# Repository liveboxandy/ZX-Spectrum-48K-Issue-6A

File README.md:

This Kicad 10 project and was only used to create an ibom with tracks to assist in the debugging of faulty boards. While the routing should be correct, the track widths have not been followed exactly, nor have component tolerances. Use at your own risk.

The ZX Spectrum Issue 6A PCB used for this has an MFG date of 8443, a silkscreen FAB revision of SRC168, a topside FAB revision of SRC166 and a solder side FAB revision of SRC167.

The created schematic was based on the physical layout of the PCB and appears to show the DC-DC circuit from a revision 4A PCB where capacitor C79 is before R79 and D19 is after R79 on the -5V line. which is not the same as the schematics available around the web show.

Note that R32 is fitted as a 0R link on this PCB.

Resistor and capacitor values in the schematic are taken from the Service Manual Revision 1.3 that was edited by Brendan Alford and appear to differ in various locations compared to various available schematics. Where they differed I have used the values from the PCB I was given by HappyLittleDiodes(Jim).

For the Ferranti ULA, do not fit R90, C100, C102, C103 and leave LK1, LK2, LK3 and LK4 open.

On the PCB I received, LKU and LKV were also open.

On the board I received,

C30 	22nF		Not Required for Saga ULA

C32 	100nF		Not Required for Saga

C35 	100nF		Not Required for Saga, Saga 10nF

C52/C53 150pF		Not Required for Saga

C67 	100pF		Not Required for Saga

C68-C71 100nF		Not Required for Saga

C76 	22nF		Not Required for Saga

C100	Not Fitted. 	For VHF 10nF

C101 	Not Fitted. 	For VHF 22nF

C102 	Not Fitted

C103 	Not Fitted

R17-R23 470R		Issue 5 Only?

R24 	1K		If TR3 is KSC839 should be 15K

R33 	680R		For Saga 560R

R34 	15R 0.5/1W

R48 	2K2		Not Required for Saga

R49 	10K		Not Required for Saga

R50 	4K7		Not Required for Saga

R51 	2K2		For Saga 1K2

R56 	1K		Not Required for Saga

R63 	1K		Not Required for Saga

R65-R67 10K		Not Required for Saga

R68 	6K8		Not Required for Saga

R69 	10K		Not Required for Saga

R73 	1K		Not Required for Saga

R74/R75 10K		Not Required for Saga

R76/R77 1K		Not Required for Saga

R80-R86 1K		Issue 5 Only?

I would not use these gerbers to manufacture a PCB without a lot more checking as that is NOT why it was done.

Have fun.

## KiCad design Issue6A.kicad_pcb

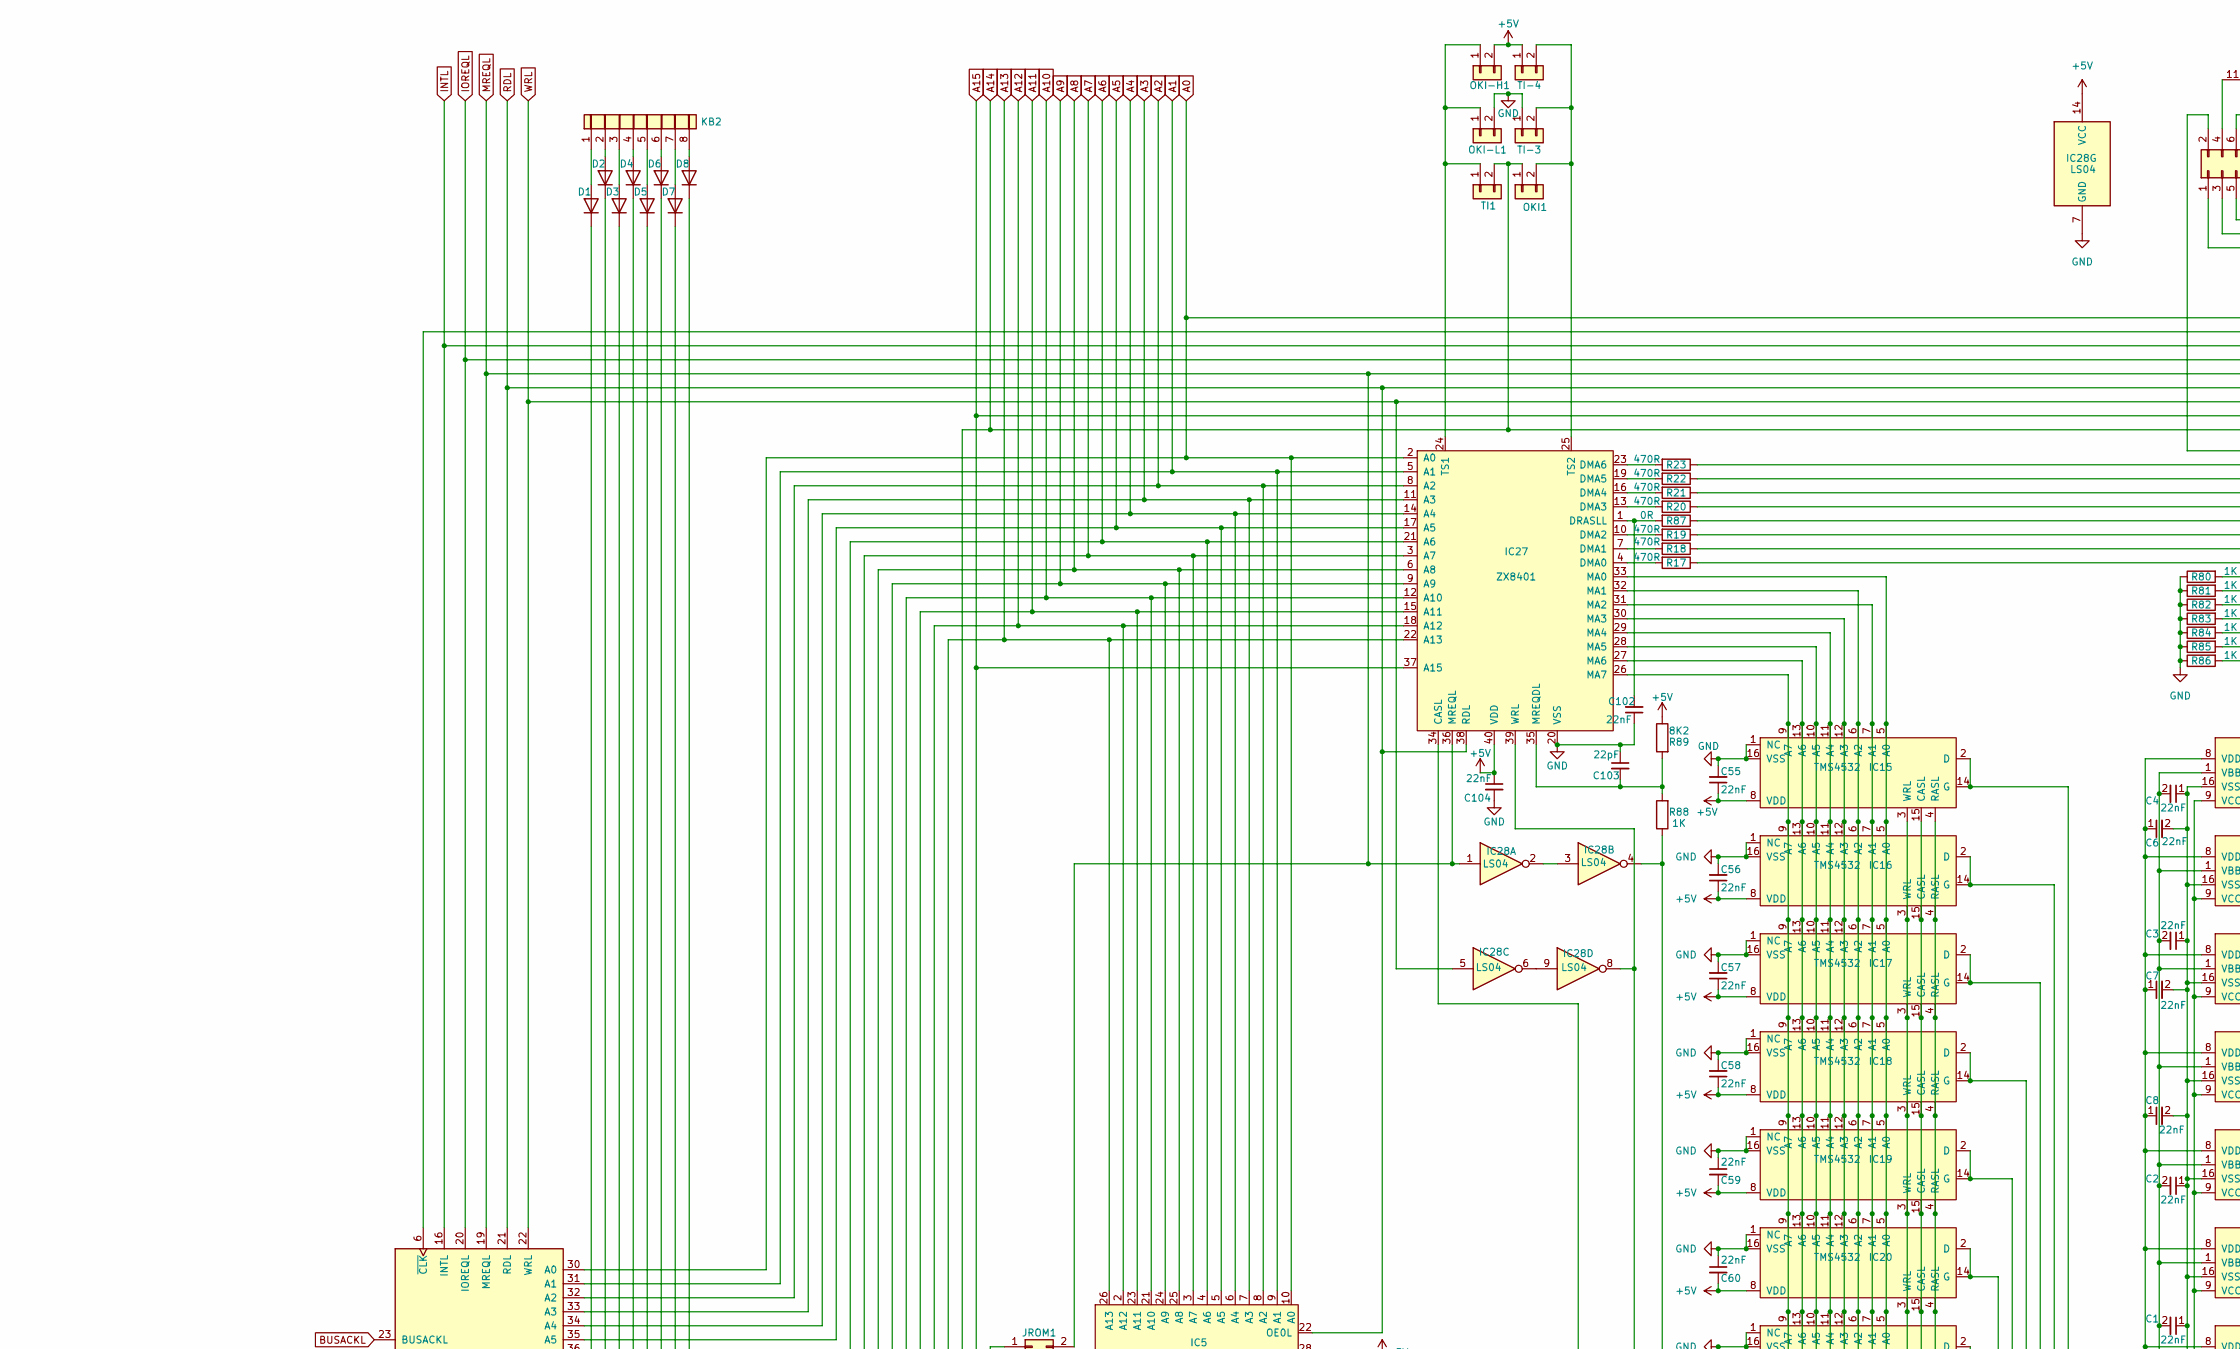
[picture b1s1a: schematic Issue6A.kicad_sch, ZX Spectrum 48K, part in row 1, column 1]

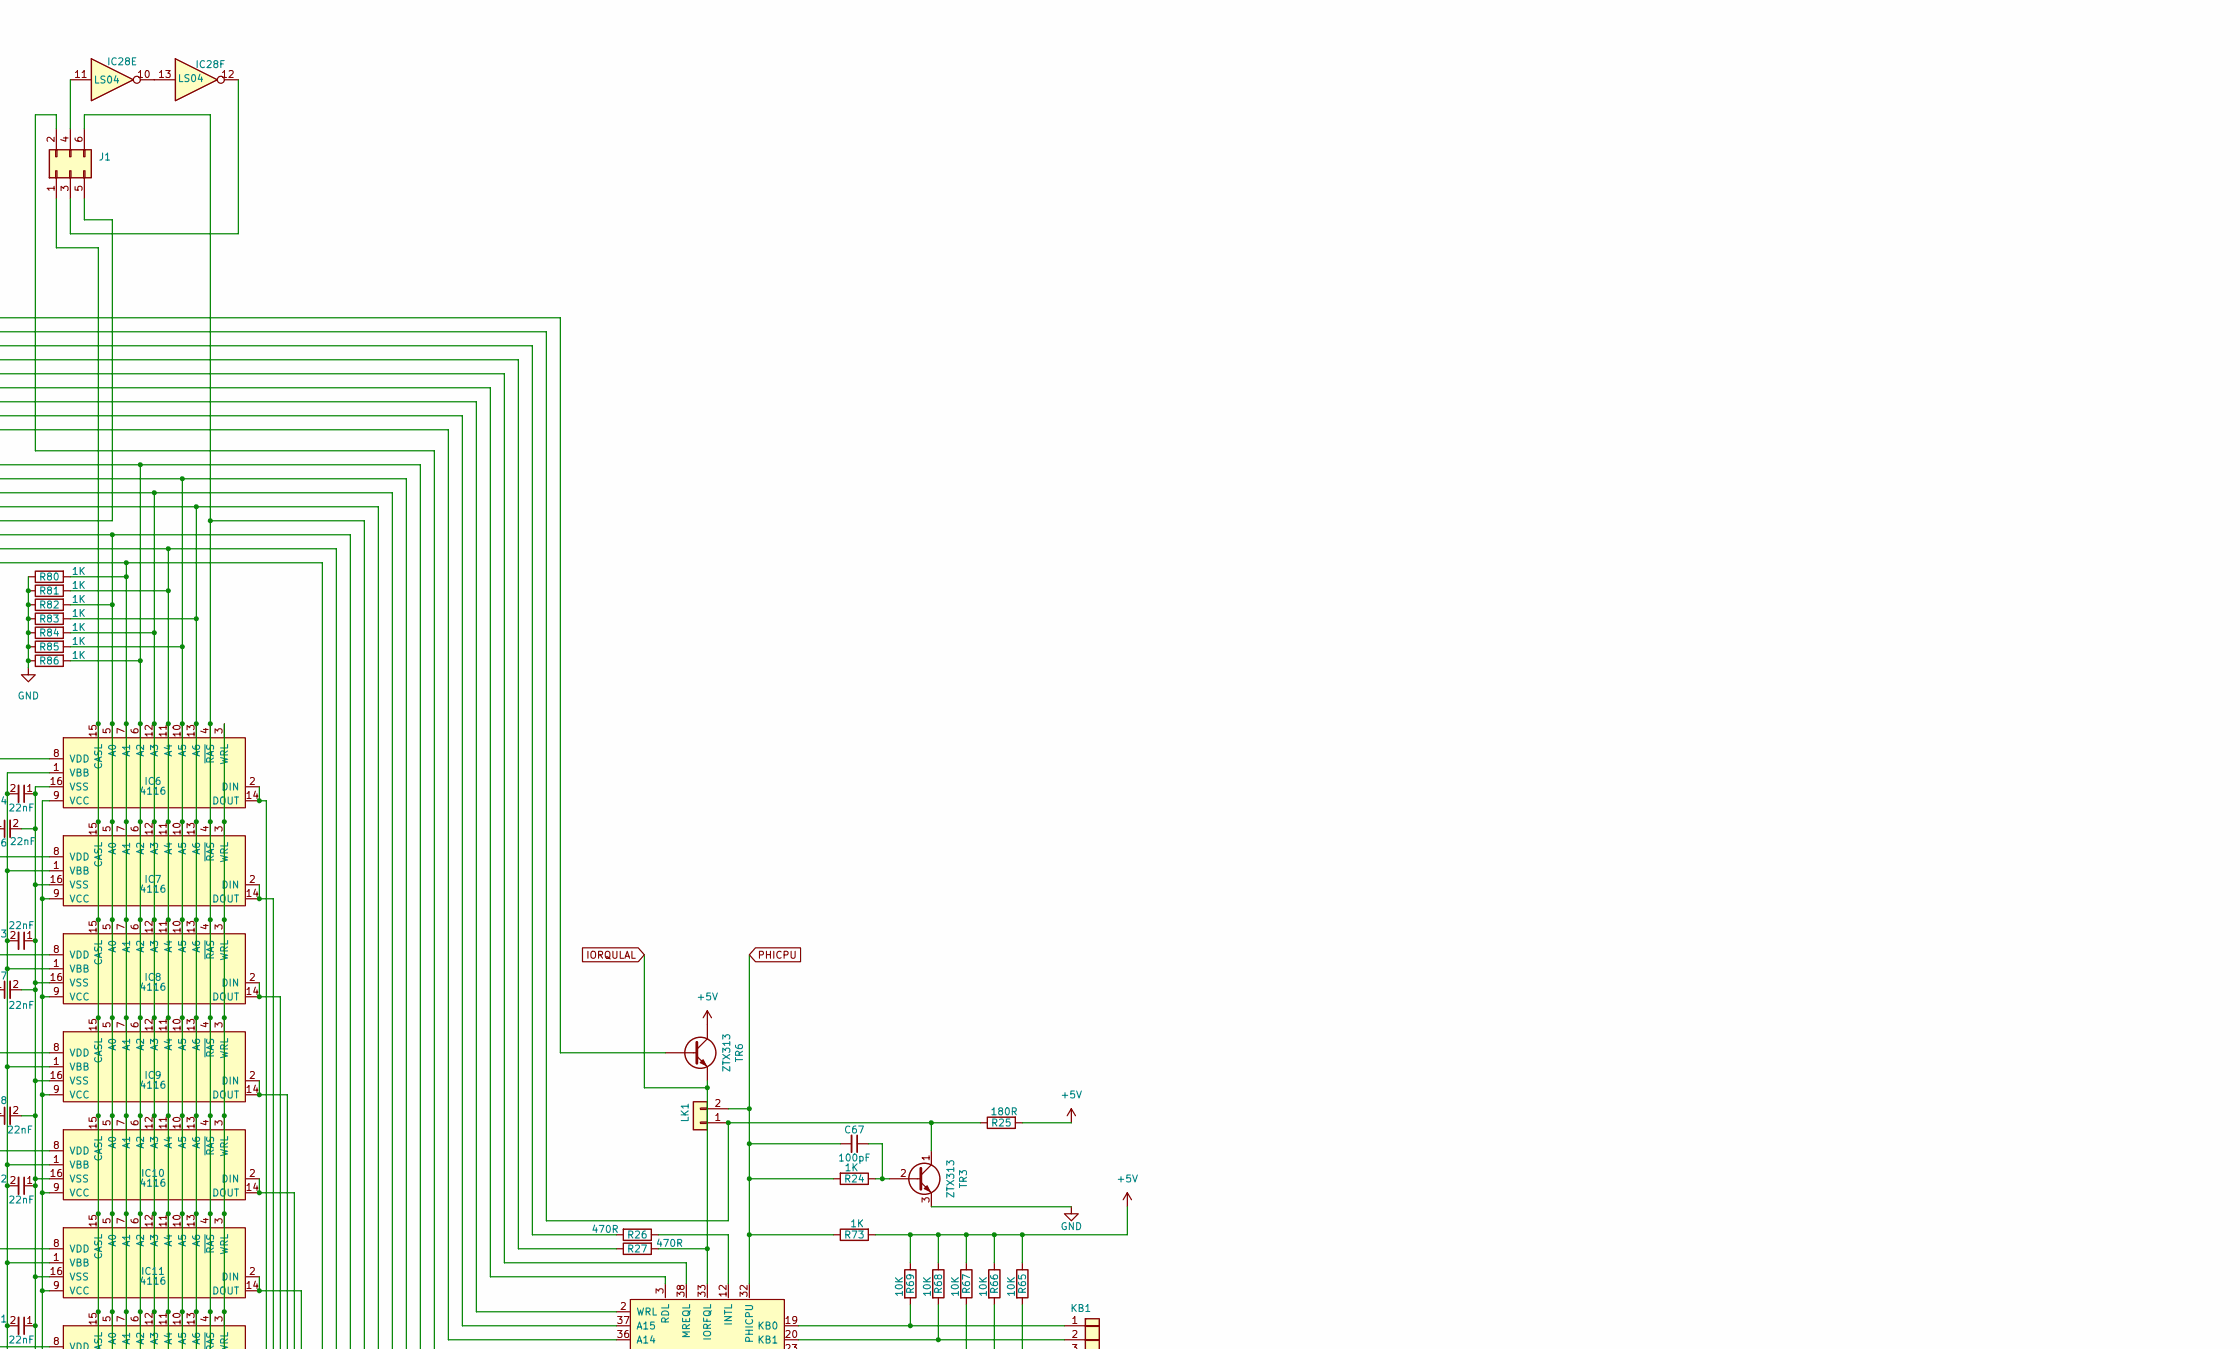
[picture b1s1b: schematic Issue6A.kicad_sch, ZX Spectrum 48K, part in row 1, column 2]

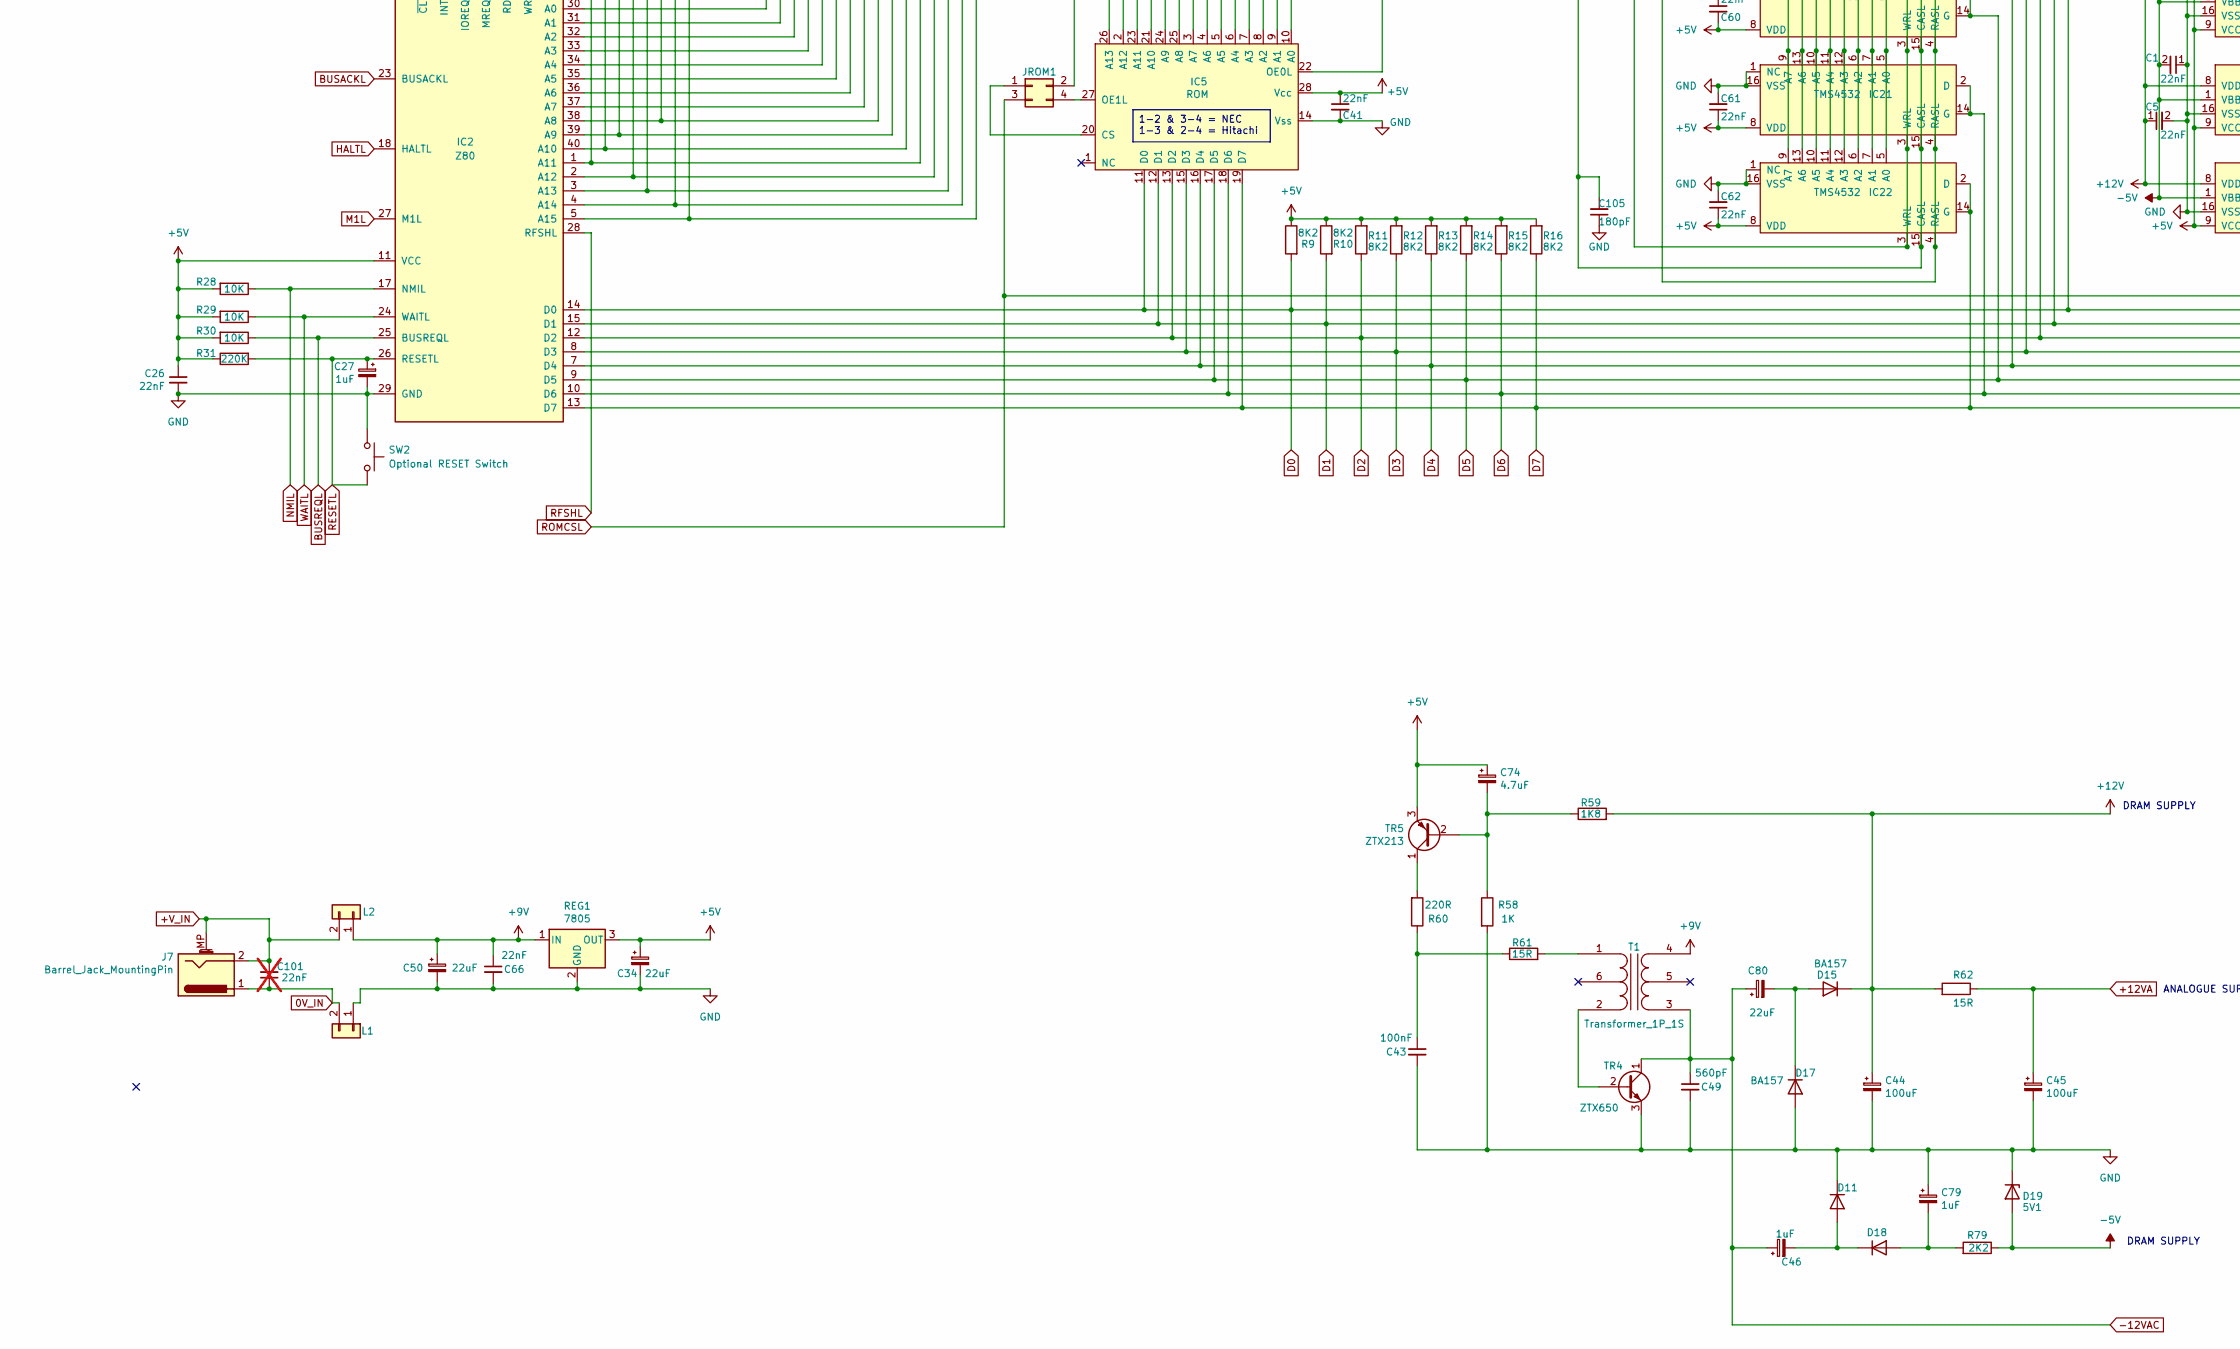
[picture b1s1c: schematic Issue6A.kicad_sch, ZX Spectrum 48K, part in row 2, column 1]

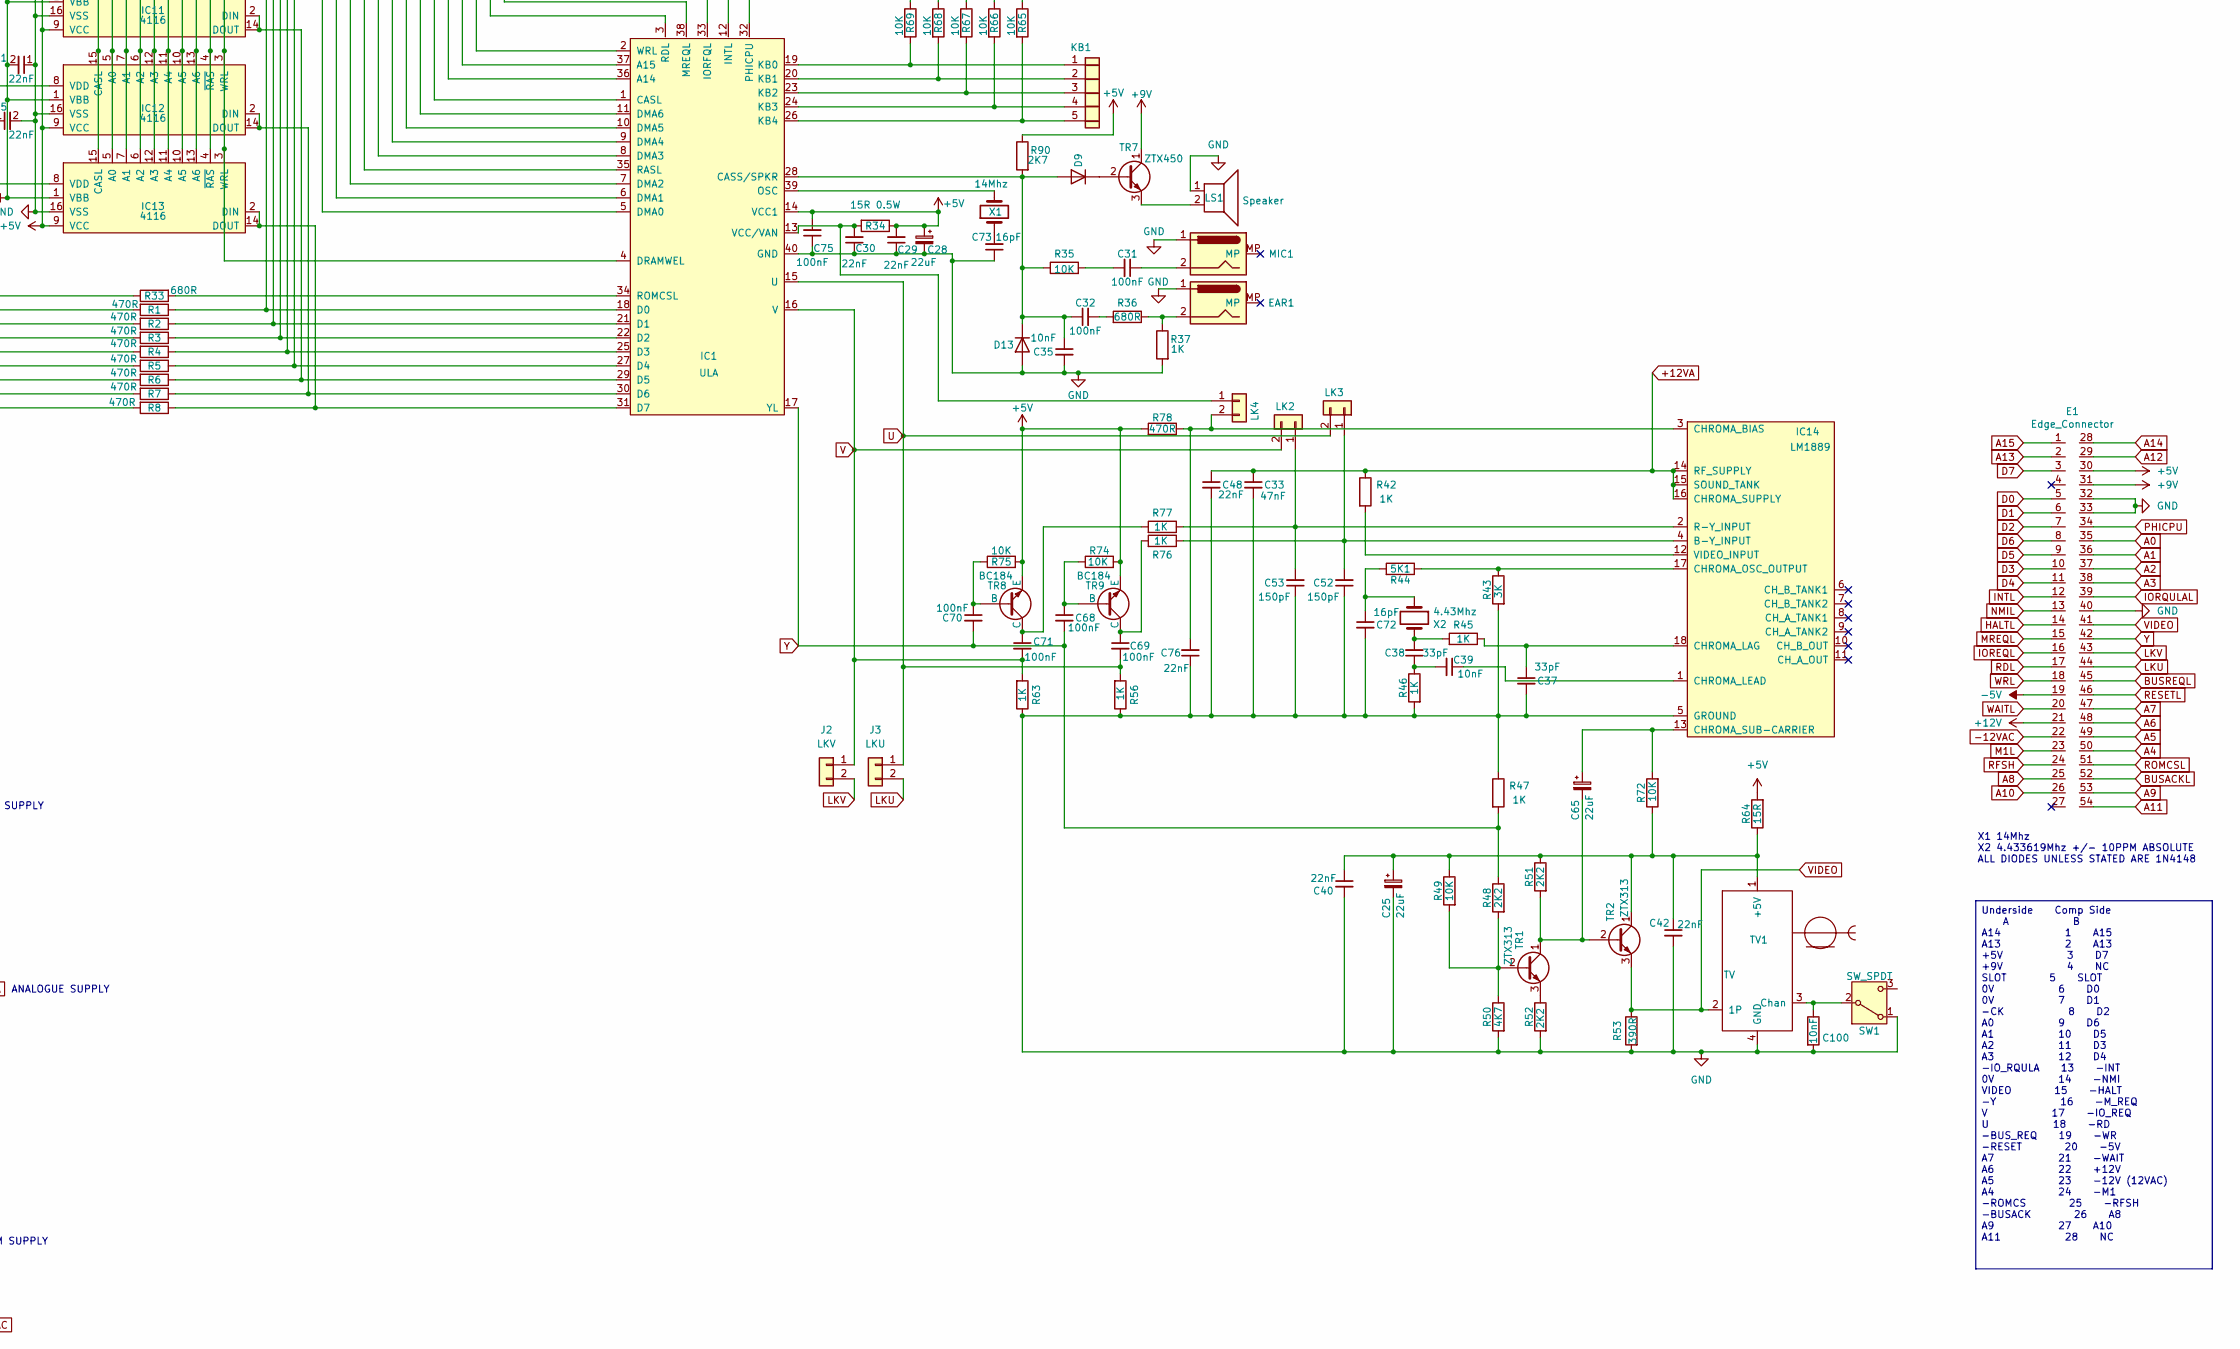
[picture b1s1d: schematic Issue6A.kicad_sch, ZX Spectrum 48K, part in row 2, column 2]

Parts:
C1, C2, C3, C4, C5, C6, C7, C8, C26, C29, C30, C40, C41, C42, C48, C55, C56, C57, C58, C59, C60, C61, C62, C66, C76, C102, C104: 22nF; C_Axial_L3.8mm_D2.6mm_P12.70mm_Horizontal
C25: 22uF; CP_Axial_L11.0mm_D6.0mm_P20.00mm_Horizontal
C27, C46, C79: 1uF; CP_Axial_L11.0mm_D6.0mm_P20.32mm_Horizontal
C28, C34, C50, C65, C80: 22uF; CP_Axial_L11.0mm_D6.0mm_P20.32mm_Horizontal
C31, C32: 100nF; C_Axial_L3.8mm_D2.6mm_P12.40mm_Horizontal
C33: 47nF; C_Axial_L3.8mm_D2.6mm_P12.70mm_Horizontal
C35: 10nF; C_Axial_L3.8mm_D2.6mm_P12.40mm_Horizontal
C37, C38: 33pF; C_Axial_L3.8mm_D2.6mm_P12.70mm_Horizontal
C39: 10nF; C_Axial_L3.8mm_D2.6mm_P12.70mm_Horizontal
C43, C68, C69, C70, C71, C75: 100nF; C_Axial_L3.8mm_D2.6mm_P12.70mm_Horizontal
C44, C45: 100uF; CP_Axial_L11.0mm_D6.0mm_P20.32mm_Horizontal
C49: 560pF; C_Axial_L3.8mm_D2.6mm_P12.70mm_Horizontal
C52, C53: 150pF; C_Axial_L3.8mm_D2.6mm_P12.70mm_Horizontal
C67: 100pF; C_Axial_L3.8mm_D2.6mm_P12.70mm_Horizontal
C72, C73: 16pF; C_Axial_L3.8mm_D2.6mm_P12.70mm_Horizontal
C74: 4.7uF; CP_Axial_L11.0mm_D6.0mm_P20.32mm_Horizontal
C100: 10nF; R_Yageo_L3.6mm_D1.6mm_P12.70mm_Horizontal
C101: 22nF; C_Axial_L3.8mm_D2.6mm_P12.70mm_Horizontal; not fitted
C103: 22pF; C_Axial_L3.8mm_D2.6mm_P12.70mm_Horizontal
C105: 180pF; C_Axial_L3.8mm_D2.6mm_P12.70mm_Horizontal
D1, D2, D3, D4, D5, D6, D7, D8, D9, D11, D18: 1N4148; D_DO-35_SOD27_P12.70mm_Horizontal
D13: 1N4148; D_DO-35_SOD27_P12.40mm_Horizontal
D15, D17: BA157; D_DO-41_SOD81_P12.70mm_Horizontal
D19: 5V1; D_DO-35_SOD27_P12.70mm_Horizontal
E1: Edge_Connector; Edge Connector
EAR1: EAR1; 3.5mm_socket
IC1: ULA; DIP-40_W15.24mm_Socket
IC2: Z80; DIP-40_W15.24mm_Socket
IC5: ROM; DIP-28_W15.24mm_Socket
IC6, IC7, IC8, IC9, IC10, IC11, IC12, IC13: 4116; DIP-16_W7.62mm_Socket
IC14: LM1889; DIP-18_W7.62mm_Socket
IC15, IC16, IC17, IC18, IC19, IC20, IC21, IC22: TMS4532; DIP-16_W7.62mm_Socket
IC27: ZX8401; DIP-40_W15.24mm_Socket
IC28: LS04; DIP-14_W7.62mm_Socket
J1: Conn_02x03_Odd_Even; RASCASLINK
J2: LKV; Link2.54
J3: LKU; Link2.54
J7: Barrel_Jack_MountingPin; BarrelJack_Horizontal
JROM1: JROM; ROM_WireLink
KB1: Keyboard5
KB2: Keyboard8
L1: L1; Wire_Link_7.62mm
L2: L2; Wire_Link_7.62mm
LK1: CLK; KEYSTONE_1430-5
LK2: LK2; Wire_Link_7.62mm
LK3: LK3; Wire_Link_7.62mm
LK4: VCC/VAN; Wire_Link_7.62mm
LS1: Speaker
MIC1: MIC1; 3.5mm_socket
OKI1: OKI; Wire_Link_7.62mm
OKI-H1: OKI-H; Wire_Link_7.62mm
OKI-L1: OKI-L; Wire_Link_7.62mm
R1, R2, R3, R4, R5, R6, R7, R8, R17, R18, R19, R20, R21, R22, R23, R26, R27, R78: 470R; R_Yageo_L3.6mm_D1.6mm_P12.70mm_Horizontal
R9, R10, R11, R12, R13, R14, R15, R16, R89: 8K2; R_Yageo_L3.6mm_D1.6mm_P12.70mm_Horizontal
R24, R42, R45, R46, R47, R56, R58, R63, R73, R76, R77, R80, R81, R82, R83, R84, R85, R86, R88: 1K; R_Yageo_L3.6mm_D1.6mm_P12.70mm_Horizontal
R25: 180R; R_Yageo_L3.6mm_D1.6mm_P12.70mm_Horizontal
R28, R29, R30, R49, R65, R66, R67, R68, R69, R72, R74, R75: 10K; R_Yageo_L3.6mm_D1.6mm_P12.70mm_Horizontal
R31: 220K; R_Yageo_L3.6mm_D1.6mm_P12.70mm_Horizontal
R33: 680R; R_Yageo_L3.6mm_D1.6mm_P12.70mm_Horizontal
R34: 15R 0.5W; R_Axial_DIN0516_L15.5mm_D5.0mm_P20.32mm_Horizontal
R35: 10K; R_Yageo_L3.6mm_D1.6mm_P12.40mm_Horizontal
R36: 680R; R_Yageo_L3.6mm_D1.6mm_P12.40mm_Horizontal
R37: 1K; R_Yageo_L3.6mm_D1.6mm_P12.40mm_Horizontal
R43: 3K; R_Yageo_L3.6mm_D1.6mm_P12.70mm_Horizontal
R44: 5K1; R_Yageo_L3.6mm_D1.6mm_P12.70mm_Horizontal
R48, R51, R52, R79: 2K2; R_Yageo_L3.6mm_D1.6mm_P12.70mm_Horizontal
R50: 4K7; R_Yageo_L3.6mm_D1.6mm_P12.70mm_Horizontal
R53: 390R; R_Yageo_L3.6mm_D1.6mm_P12.70mm_Horizontal
R59: 1K8; R_Yageo_L3.6mm_D1.6mm_P12.70mm_Horizontal
R60: 220R; R_Yageo_L3.6mm_D1.6mm_P12.70mm_Horizontal
R61, R62, R64: 15R; R_Yageo_L3.6mm_D1.6mm_P12.70mm_Horizontal
R87: 0R; R_Yageo_L3.6mm_D1.6mm_P12.70mm_Horizontal
R90: 2K7; R_Yageo_L3.6mm_D1.6mm_P12.70mm_Horizontal
REG1: 7805; TO-220-3_Horizontal_TabDown
SW1: SW_SPDT; SHM1260H
SW2: Optional RESET Switch; PinHeader_1x02_P2.54mm_Vertical
T1: Transformer_1P_1S; Coil
TI1: TI; Wire_Link_7.62mm
TI-3: TI-3; Wire_Link_7.62mm
TI-4: TI-4; Wire_Link_7.62mm
TR1, TR2, TR3, TR6: ZTX313; TO-92Flat
TR4: ZTX650; TO-92Flat
TR5: ZTX213; TO-92Flat
TR7: ZTX450; TO-92Flat
TR8, TR9: BC184; TR9
TV1: TV; Modulator4B
X1: 14Mhz; X1
X2: 4.43Mhz; X2

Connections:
0V_IN: C101.1, J7.1, L1.2
+5V: C26.1, C28.1, C29.2, C34.1, C41.1, C55.1, C56.1, C57.1, C58.1, C59.2, C60.2, C61.1, C62.1, C74.1, C75.2, C104.1, E1.30, IC1.14 (VCC1), IC2.11 (VCC), IC5.28 (Vcc), IC6.9 (VCC), IC7.9 (VCC), IC8.9 (VCC), IC9.9 (VCC), IC10.9 (VCC), IC11.9 (VCC), IC12.9 (VCC), IC13.9 (VCC), IC15.8 (VDD), IC16.8 (VDD), IC17.8 (VDD), IC18.8 (VDD), IC19.8 (VDD), IC20.8 (VDD), IC21.8 (VDD), IC22.8 (VDD), IC27.40 (VDD), IC28.14 (VCC), OKI-H1.2, R9.1, R10.1, R11.2, R12.2, R13.2, R14.2, R15.2, R16.2, R25.2, R28.2, R29.2, R30.2, R31.1, R34.1, R64.2, R65.1, R66.1, R67.1, R68.1, R69.1, R73.2, R74.2, R75.2, R78.2, R89.1, R90.1, REG1.3 (OUT), TI-4.1, TR5.3 (E), TR6.1 (C), TR8.3 (E), TR9.3 (E)
+9V: C50.1, C66.1, E1.31, L2.1, REG1.1 (IN), T1.4 (SB), TR7.1 (C)
+12V: C5.1, C6.1, C7.1, C8.1, C44.1, D15.1 (K), E1.21, IC6.8 (VDD), IC7.8 (VDD), IC8.8 (VDD), IC9.8 (VDD), IC10.8 (VDD), IC11.8 (VDD), IC12.8 (VDD), IC13.8 (VDD), R59.2, R62.2
+12VA: C33.1, C45.1, C48.1, IC14.14 (RF_SUPPLY), IC14.15 (SOUND_TANK), IC14.16 (CHROMA_SUPPLY), R42.1, R62.1
+V_IN: C101.2, J7.2, J7.MP (MountPin_MP), L2.2
-5V: C1.2, C2.2, C3.2, C4.2, D19.2 (A), E1.19, IC6.1 (VBB), IC7.1 (VBB), IC8.1 (VBB), IC9.1 (VBB), IC10.1 (VBB), IC11.1 (VBB), IC12.1 (VBB), IC13.1 (VBB), R79.1
-12VAC: C46.1, C49.1, C80.1, E1.22, T1.3 (SA), TR4.1 (C)
A0: E1.35, IC2.30 (A0), IC5.10 (A0), IC27.2 (A0), TR6.2 (B)
A1: E1.36, IC2.31 (A1), IC5.9 (A1), IC27.5 (A1)
A2: E1.37, IC2.32 (A2), IC5.8 (A2), IC27.8 (A2)
A3: E1.38, IC2.33 (A3), IC5.7 (A3), IC27.11 (A3)
A4: E1.50, IC2.34 (A4), IC5.6 (A4), IC27.14 (A4)
A5: E1.49, IC2.35 (A5), IC5.5 (A5), IC27.17 (A5)
A6: E1.48, IC2.36 (A6), IC5.4 (A6), IC27.21 (A6)
A7: E1.47, IC2.37 (A7), IC5.3 (A7), IC27.3 (A7)
A8: D6.1 (K), E1.25, IC2.38 (A8), IC5.25 (A8), IC27.6 (A8)
A9: D3.1 (K), E1.53, IC2.39 (A9), IC5.24 (A9), IC27.9 (A9)
A10: D2.1 (K), E1.26, IC2.40 (A10), IC5.21 (A10), IC27.12 (A10)
A11: D1.1 (K), E1.54, IC2.1 (A11), IC5.23 (A11), IC27.15 (A11)
A12: D4.1 (K), E1.29, IC2.2 (A12), IC5.2 (A12), IC27.18 (A12)
A13: D5.1 (K), E1.2, IC2.3 (A13), IC5.26 (A13), IC27.22 (A13)
A14: D7.1 (K), E1.28, IC1.36 (A14), IC2.4 (A14), OKI1.1, TI1.2
A15: D8.1 (K), E1.1, IC1.37 (A15), IC2.5 (A15), IC27.37 (A15)
BUSACKL: E1.52, IC2.23 (BUSACKL)
BUSREQL: E1.45, IC2.25 (BUSREQL), R30.1
D0: E1.5, IC2.14 (D0), IC5.11 (D0), IC15.2 (D), IC15.14 (G), R1.2, R9.2
D1: E1.6, IC2.15 (D1), IC5.12 (D1), IC16.2 (D), IC16.14 (G), R2.2, R10.2
D2: E1.7, IC2.12 (D2), IC5.13 (D2), IC17.2 (D), IC17.14 (G), R3.2, R11.1
D3: E1.10, IC2.8 (D3), IC5.15 (D3), IC18.2 (D), IC18.14 (G), R4.2, R12.1
D4: E1.11, IC2.7 (D4), IC5.16 (D4), IC19.2 (D), IC19.14 (G), R5.2, R13.1
D5: E1.9, IC2.9 (D5), IC5.17 (D5), IC20.2 (D), IC20.14 (G), R6.2, R14.1
D6: E1.8, IC2.10 (D6), IC5.18 (D6), IC21.2 (D), IC21.14 (G), R7.2, R15.1
D7: E1.3, IC2.13 (D7), IC5.19 (D7), IC22.2 (D), IC22.14 (G), R8.2, R16.1
GND: C1.1, C2.1, C3.1, C4.1, C5.2, C6.2, C7.2, C8.2, C25.2, C26.2, C27.2, C28.2, C29.1, C30.1, C33.2, C34.2, C35.2, C37.2, C40.2, C41.2, C42.2, C43.2, C44.2, C45.2, C48.2, C49.2, C50.2, C52.1, C53.1, C55.2, C56.2, C57.2, C58.2, C59.1, C60.1, C61.2, C62.2, C66.2, C72.2, C73.1, C75.1, C76.1, C79.1, C100.2, C102.1, C103.1, C104.2, C105.1, D11.1 (K), D13.2 (A), D17.2 (A), D19.1 (K), E1.32, E1.33, E1.40, EAR1.1, IC1.40 (GND), IC2.29 (GND), IC5.14 (Vss), IC6.16 (VSS), IC7.16 (VSS), IC8.16 (VSS), IC9.16 (VSS), IC10.16 (VSS), IC11.16 (VSS), IC12.16 (VSS), IC13.16 (VSS), IC14.5 (GROUND), IC15.1 (NC), IC15.16 (VSS), IC16.1 (NC), IC16.16 (VSS), IC17.1 (NC), IC17.16 (VSS), IC18.1 (NC), IC18.16 (VSS), IC19.1 (NC), IC19.16 (VSS), IC20.1 (NC), IC20.16 (VSS), IC21.1 (NC), IC21.16 (VSS), IC22.1 (NC), IC22.16 (VSS), IC27.20 (VSS), IC28.7 (GND), L1.1, LS1.1, MIC1.1, OKI-L1.2, R37.2, R43.2, R46.2, R47.1, R50.2, R52.2, R53.2, R56.1, R58.2, R63.1, R80.1, R81.1, R82.1, R83.1, R84.1, R85.1, R86.1, REG1.2 (GND), SW1.1 (A), SW2.1, TI-3.1, TR3.3 (E), TR4.3 (E), TV1.4 (GND)
HALTL: E1.14, IC2.18 (HALTL)
INTL: E1.12, IC2.16 (INTL), R26.2
IOREQL: E1.16, IC2.20 (IOREQL), R27.1
IORQULAL: E1.39, IC1.33 (IORFQL), R27.2, TR6.3 (E)
LKU: E1.44, J3.2
LKV: E1.43, J2.2
M1L: E1.23, IC2.27 (M1L)
MREQL: E1.15, IC1.38 (MREQL), IC2.19 (MREQL), IC27.36 (MREQL), IC28.1, JROM1.2
NMIL: E1.13, IC2.17 (NMIL), R28.1
unnamed: C31.1, MIC1.2
unnamed: C31.2, R35.2
unnamed: C32.2, R36.2
unnamed: C38.1, C39.2, R46.1
unnamed: C38.2, R45.2, X2.2
unnamed: C43.1, R60.1, R61.1
unnamed: C72.1, R44.2, X2.1
unnamed: C73.2, X1.1
unnamed: D1.2 (A), KB2.1
unnamed: D2.2 (A), KB2.2
unnamed: D3.2 (A), KB2.3
unnamed: D4.2 (A), KB2.4
unnamed: D5.2 (A), KB2.5
unnamed: D6.2 (A), KB2.6
unnamed: D7.2 (A), KB2.7
unnamed: D8.2 (A), KB2.8
unnamed: D9.1 (K), TR7.2 (B)
unnamed: C46.2, D11.2 (A), D18.1 (K)
unnamed: C32.1, C35.1, D9.2 (A), D13.1 (K), IC1.28 (CASS/SPKR), R35.1, R90.2
unnamed: C80.2, D15.2 (A), D17.1 (K)
unnamed: C79.2, D18.2 (A), R79.2
unnamed: EAR1.2, R36.1, R37.1
unnamed: IC1.1 (CASL), J1.2
unnamed: IC1.18 (D0), IC6.2 (DIN), IC6.14 (DOUT), R1.1
unnamed: IC1.21 (D1), IC7.2 (DIN), IC7.14 (DOUT), R2.1
unnamed: IC1.22 (D2), IC8.2 (DIN), IC8.14 (DOUT), R3.1
unnamed: IC1.25 (D3), IC9.2 (DIN), IC9.14 (DOUT), R4.1
unnamed: IC1.27 (D4), IC10.2 (DIN), IC10.14 (DOUT), R5.1
unnamed: IC1.29 (D5), IC11.2 (DIN), IC11.14 (DOUT), R6.1
unnamed: IC1.30 (D6), IC12.2 (DIN), IC12.14 (DOUT), R7.1
unnamed: IC1.31 (D7), IC13.2 (DIN), IC13.14 (DOUT), R8.1
unnamed: IC1.5 (DMA0), IC6.7 (A1), IC7.7 (A1), IC8.7 (A1), IC9.7 (A1), IC10.7 (A1), IC11.7 (A1), IC12.7 (A1), IC13.7 (A1), R17.1, R80.2
unnamed: IC1.6 (DMA1), IC6.11 (A4), IC7.11 (A4), IC8.11 (A4), IC9.11 (A4), IC10.11 (A4), IC11.11 (A4), IC12.11 (A4), IC13.11 (A4), R18.1, R81.2
unnamed: IC1.7 (DMA2), IC6.5 (A0), IC7.5 (A0), IC8.5 (A0), IC9.5 (A0), IC10.5 (A0), IC11.5 (A0), IC12.5 (A0), IC13.5 (A0), R19.1, R82.2
unnamed: IC1.8 (DMA3), IC6.13 (A6), IC7.13 (A6), IC8.13 (A6), IC9.13 (A6), IC10.13 (A6), IC11.13 (A6), IC12.13 (A6), IC13.13 (A6), R20.1, R83.2
unnamed: IC1.9 (DMA4), IC6.12 (A3), IC7.12 (A3), IC8.12 (A3), IC9.12 (A3), IC10.12 (A3), IC11.12 (A3), IC12.12 (A3), IC13.12 (A3), R21.1, R84.2
unnamed: IC1.10 (DMA5), IC6.10 (A5), IC7.10 (A5), IC8.10 (A5), IC9.10 (A5), IC10.10 (A5), IC11.10 (A5), IC12.10 (A5), IC13.10 (A5), R22.1, R85.2
unnamed: IC1.11 (DMA6), IC6.6 (A2), IC7.6 (A2), IC8.6 (A2), IC9.6 (A2), IC10.6 (A2), IC11.6 (A2), IC12.6 (A2), IC13.6 (A2), R23.1, R86.2
unnamed: IC1.4 (DRAMWEL), IC6.3 (WRL), IC7.3 (WRL), IC8.3 (WRL), IC9.3 (WRL), IC10.3 (WRL), IC11.3 (WRL), IC12.3 (WRL), IC13.3 (WRL)
unnamed: IC1.12 (INTL), R26.1
unnamed: IC1.19 (KB0), KB1.1, R69.2
unnamed: IC1.20 (KB1), KB1.2, R68.2
unnamed: IC1.23 (KB2), KB1.3, R67.2
unnamed: IC1.24 (KB3), KB1.4, R66.2
unnamed: IC1.26 (KB4), KB1.5, R65.2
unnamed: IC1.39 (OSC), X1.2
unnamed: IC1.35 (RASL), IC6.4 (~RAS), IC7.4 (~RAS), IC8.4 (~RAS), IC9.4 (~RAS), IC10.4 (~RAS), IC11.4 (~RAS), IC12.4 (~RAS), IC13.4 (~RAS), J1.6
unnamed: IC1.34 (ROMCSL), R33.2
unnamed: C30.2, IC1.13 (VCC/VAN), LK4.1, R34.2
unnamed: IC2.6 (~CLK), LK1.1, R25.1, TR3.1 (C)
unnamed: IC5.20 (CS), JROM1.1
unnamed: IC5.27 (OE1L), JROM1.4
unnamed: IC6.15 (CASL), IC7.15 (CASL), IC8.15 (CASL), IC9.15 (CASL), IC10.15 (CASL), IC11.15 (CASL), IC12.15 (CASL), IC13.15 (CASL), J1.1
unnamed: C52.2, IC14.4 (B-Y_INPUT), LK3.1, R76.1
unnamed: C76.2, IC14.3 (CHROMA_BIAS), LK4.2, R78.1
unnamed: C37.1, IC14.18 (CHROMA_LAG), R45.1
unnamed: C39.1, IC14.1 (CHROMA_LEAD)
unnamed: IC14.17 (CHROMA_OSC_OUTPUT), R43.1, R44.1
unnamed: C65.1, IC14.13 (CHROMA_SUB-CARRIER), R72.2
unnamed: C53.2, IC14.2 (R-Y_INPUT), LK2.1, R77.1
unnamed: IC14.12 (VIDEO_INPUT), R42.2
unnamed: IC15.5 (A0), IC16.5 (A0), IC17.5 (A0), IC18.5 (A0), IC19.5 (A0), IC20.5 (A0), IC21.5 (A0), IC22.5 (A0), IC27.33 (MA0)
unnamed: IC15.7 (A1), IC16.7 (A1), IC17.7 (A1), IC18.7 (A1), IC19.7 (A1), IC20.7 (A1), IC21.7 (A1), IC22.7 (A1), IC27.31 (MA2)
unnamed: IC15.6 (A2), IC16.6 (A2), IC17.6 (A2), IC18.6 (A2), IC19.6 (A2), IC20.6 (A2), IC21.6 (A2), IC22.6 (A2), IC27.32 (MA1)
unnamed: IC15.12 (A3), IC16.12 (A3), IC17.12 (A3), IC18.12 (A3), IC19.12 (A3), IC20.12 (A3), IC21.12 (A3), IC22.12 (A3), IC27.30 (MA3)
unnamed: IC15.11 (A4), IC16.11 (A4), IC17.11 (A4), IC18.11 (A4), IC19.11 (A4), IC20.11 (A4), IC21.11 (A4), IC22.11 (A4), IC27.29 (MA4)
unnamed: IC15.10 (A5), IC16.10 (A5), IC17.10 (A5), IC18.10 (A5), IC19.10 (A5), IC20.10 (A5), IC21.10 (A5), IC22.10 (A5), IC27.28 (MA5)
unnamed: IC15.13 (A6), IC16.13 (A6), IC17.13 (A6), IC18.13 (A6), IC19.13 (A6), IC20.13 (A6), IC21.13 (A6), IC22.13 (A6), IC27.27 (MA6)
unnamed: IC15.9 (A7), IC16.9 (A7), IC17.9 (A7), IC18.9 (A7), IC19.9 (A7), IC20.9 (A7), IC21.9 (A7), IC22.9 (A7), IC27.26 (MA7)
unnamed: C105.2, IC15.15 (CASL), IC16.15 (CASL), IC17.15 (CASL), IC18.15 (CASL), IC19.15 (CASL), IC20.15 (CASL), IC21.15 (CASL), IC22.15 (CASL), IC27.34 (CASL)
unnamed: IC15.4 (RASL), IC16.4 (RASL), IC17.4 (RASL), IC18.4 (RASL), IC19.4 (RASL), IC20.4 (RASL), IC21.4 (RASL), IC22.4 (RASL), IC28.4, R88.1
unnamed: IC15.3 (WRL), IC16.3 (WRL), IC17.3 (WRL), IC18.3 (WRL), IC19.3 (WRL), IC20.3 (WRL), IC21.3 (WRL), IC22.3 (WRL), IC27.39 (WRL), IC28.8
unnamed: IC27.4 (DMA0), R17.2
unnamed: IC27.7 (DMA1), R18.2
unnamed: IC27.10 (DMA2), R19.2
unnamed: IC27.13 (DMA3), R20.2
unnamed: IC27.16 (DMA4), R21.2
unnamed: IC27.19 (DMA5), R22.2
unnamed: IC27.23 (DMA6), R23.2
unnamed: C102.2, IC27.1 (DRASLL), R87.2
unnamed: C103.2, IC27.35 (MREQDL), R88.2, R89.2
unnamed: IC27.24 (TS1), OKI-H1.1, OKI-L1.1, TI1.1
unnamed: IC27.25 (TS2), OKI1.2, TI-3.2, TI-4.2
unnamed: IC28.2, IC28.3
unnamed: IC28.6, IC28.9
unnamed: IC28.10, IC28.13
unnamed: IC28.12, J1.3
unnamed: IC28.11, J1.4
unnamed: J1.5, R87.1
unnamed: C100.1, SW1.2 (B), TV1.3 (Chan)
unnamed: R61.2, T1.1 (AA)
unnamed: T1.2 (AB), TR4.2 (B)
unnamed: R48.2, R49.2, R50.1, TR1.2 (B)
unnamed: C65.2, R51.2, TR1.1 (C), TR2.2 (B)
unnamed: R52.1, TR1.3 (E)
unnamed: C25.1, C40.1, C42.1, R49.1, R51.1, R64.1, R72.1, TR2.1 (C), TV1.1 (+5V)
unnamed: C67.1, R24.1, TR3.2 (B)
unnamed: C74.2, R58.1, R59.1, TR5.2 (B)
unnamed: R60.2, TR5.1 (C)
unnamed: LS1.2, TR7.3 (E)
unnamed: C70.1, R75.1, TR8.2 (B)
unnamed: C71.1, R77.2, TR8.1 (C)
unnamed: C68.1, R74.1, TR9.2 (B)
unnamed: C69.1, R76.2, TR9.1 (C)
PHICPU: C67.2, E1.34, IC1.32 (PHICPU), LK1.2, R24.2, R73.1
RDL: E1.17, IC1.3 (RDL), IC2.21 (RDL), IC5.22 (OE0L), IC27.38 (RDL)
RESETL: C27.1, E1.46, IC2.26 (RESETL), R31.2, SW2.2
RFSH: E1.24
RFSHL: IC2.28 (RFSHL)
ROMCSL: E1.51, JROM1.3, R33.1
U: C69.2, IC1.15 (U), J3.1, LK3.2, R56.2
V: C71.2, IC1.16 (V), J2.1, LK2.2, R63.2
VIDEO: E1.41, R53.1, TR2.3 (E), TV1.2 (1P)
WAITL: E1.20, IC2.24 (WAITL), R29.1
WRL: E1.18, IC1.2 (WRL), IC2.22 (WRL), IC28.5
Y: C68.2, C70.2, E1.42, IC1.17 (YL), R47.2, R48.1

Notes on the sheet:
X1 14Mhz X2 4.433619Mhz +/- 10PPM ABSOLUTE ALL DIODES UNLESS STATED ARE 1N4148
DRAM SUPPLY
ANALOGUE SUPPLY
Underside Comp Side A B A14 1 A15 A13 2 A13 +5V 3 D7 +9V 4 NC SLOT 5 SLOT 0V 6 D0 0V 7 D1 -CK 8 D2 A0 9 D6 A1 10 D5 A2 11 D3 A3 12 D4 -IO_RQULA 13 -INT 0V 14 -NMI VIDEO 15 -HALT -Y 16 -M_REQ V 17 -IO_REQ U 18 -RD -BUS_REQ 19 -WR -RESET 20 -5V A7 21 -WAIT A6 22 +12V A5 23 -12V (12VAC) A4 24 -M1 -ROM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
1-2 & 3-4 = NEC 1-3 & 2-4 = Hitachi

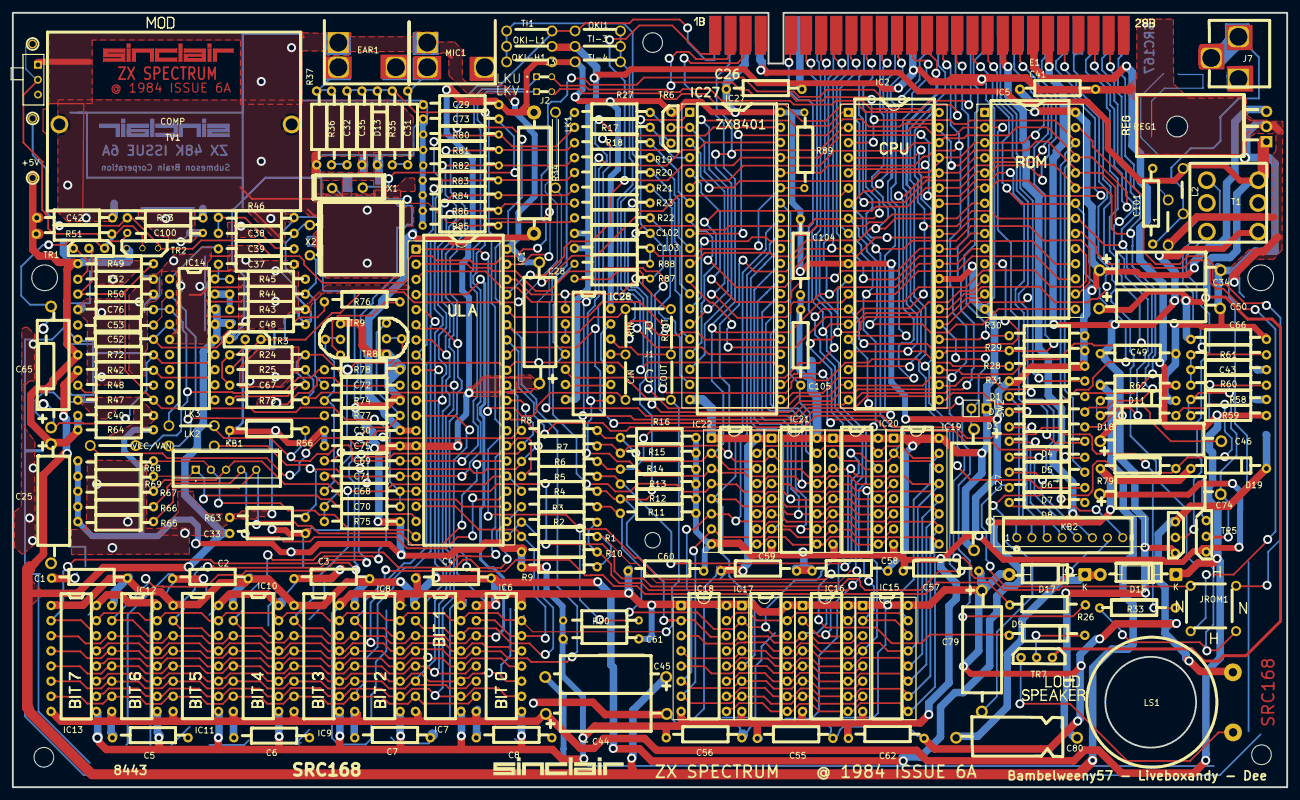
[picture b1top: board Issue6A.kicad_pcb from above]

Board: 2 copper layers, 214.0 x 130.0 mm, 218 parts (0 on the bottom side), 158 nets.
